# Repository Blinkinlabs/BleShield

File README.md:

# Blinkinlabs Bluetooth Low Energy Shield

An Arduino shield using the S-Power BG312L BLE module:
http://s-power.com.hk/BG312L.html

This shield is designed for the serial version of the module.

The BLE Shield has plenty of different peripherals that you can use to prototype your own Bluetooth Low Energy designs: three buttons, one RGB led, and an output to control one digital RGB LED strip.

The BLE Shield has been tested on the Arduino Duemilanove, Uno, and Leonardo. It has been confirmed to work with the iPad Mini running the free LightBlue application, and should work fine with iPhone 4S, iPhone5, and iPad Retina running iOS 5 and 6. The iPad 2 does not support Bluetooth 4.0 (BLE). Android support for BLE is unfortunately incomplete but in active development. Support for MacOS, Windows, and Linux is currently untested but seems to be in active development.

We're currently working on demo applications for iOS and computers, but in the mean time, you can communicate with your BLE Shield using the free LightBlue application by Punch Through, available on the app store. There are several other BLE iOS apps available that should work as well.

The BG312L module is based on the [TI CC2541][ti] Bluetooth 4.0 chip. More information, as well as sample iOS code, is available on [TI's Wiki][ti-wiki].

Let us know what cool things you do with the BLE Shield!

# Arduino Library and Demo Sketch

From the `library` folder, copy the `Blinkinlabs_BLEShield` folder to your Arduino `libraries` folder. Restart the Arduino IDE, then open File->Sketchbook->libraries->Blinkinlabs_BLEShield->BLEShield. Upload to your Arduino and follow the instructions on our [website][ble] to connect to the shield using your Bluetooth 4.0 compatible device. Enjoy!

[ti]: http://www.ti.com/product/cc2541
[ti-wiki]: http://processors.wiki.ti.com/index.php/Category:BluetoothLE

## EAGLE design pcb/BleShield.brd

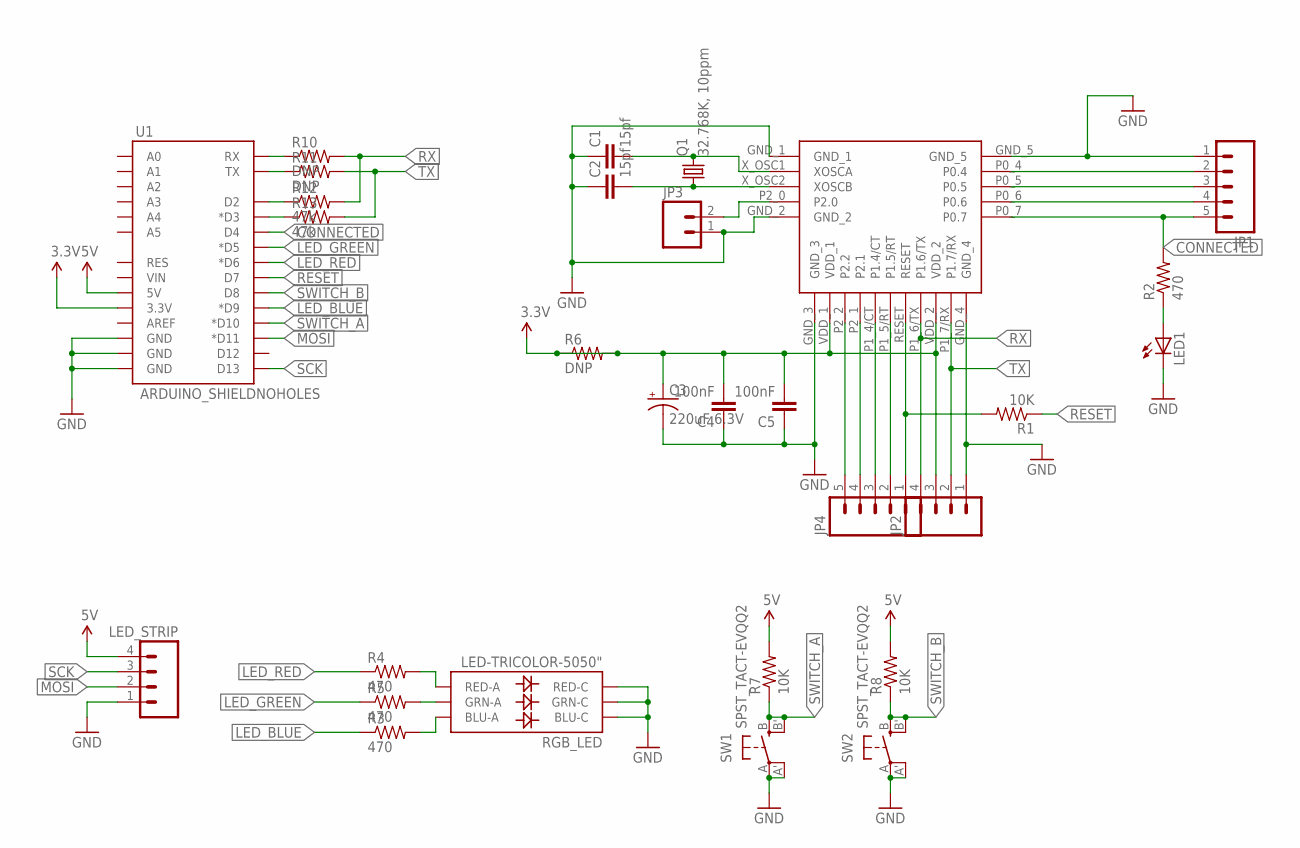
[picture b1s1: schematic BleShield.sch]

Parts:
C1, C2: 15pf; 0805
C3: 220uF 6.3V; C/6032-28R
C4, C5: 100nF; 0805
JP1, JP4: M051.27MM; 1X05-1.27MM
JP2: M041.27MM; 1X04-1.27MM
JP3: M02; 1X02-1.27MM
LED1: LEDCHIPLED_0805; CHIPLED_0805
LED_STRIP: M04PTH; 1X04
Q1: 32.768K, 10ppm; CRYSTAL_3215
R1, R7, R8: 10K; 0805
R2, R3, R4, R5: 470; 0805
R6, R10, R11: DNP; 0805
R12, R13: 47k; 0805
RGB_LED: LED-TRICOLOR-5050"; LED-TRICOLOR-5050-FIXED
SW1, SW2: SPST_TACT-EVQQ2; EVQ-Q2
U1: ARDUINO_SHIELDNOHOLES; DUEMILANOVE_SHIELD_NOHOLES
U$1: BG213L; BG312L

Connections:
3.3V: C3.+, C4.2, C5.2, JP2.3, R6.1, R6.2, U1.3.3V, U$1.VDD_1, U$1.VDD_2
5V: LED_STRIP.4, R7.2, R8.2, U1.5V
CONNECTED: JP1.5, R2.2, U1.D4, U$1.P0_7 (P0.7)
GND: C1.1, C2.1, C3.-, C4.1, C5.1, JP1.1, JP2.1, JP3.1, LED1.C, LED_STRIP.1, RGB_LED.1 (BLU-C), RGB_LED.2 (RED-C), RGB_LED.3 (GRN-C), SW1.A, SW1.A' (P1), SW2.A, SW2.A' (P1), U1.GND@0 (GND), U1.GND@1 (GND), U1.GND@2 (GND), U$1.GND_1, U$1.GND_2, U$1.GND_3, U$1.GND_4, U$1.GND_5
LED_BLUE: R3.1, U1.D9 (*D9)
LED_GREEN: R5.1, U1.D5 (*D5)
LED_RED: R4.1, U1.D6 (*D6)
MOSI: LED_STRIP.2, U1.D11 (*D11)
unnamed: JP4.1, R1.2, U$1.RESET
unnamed: R3.2, RGB_LED.6 (BLU-A)
unnamed: C1.2, Q1.P$2 (2), U$1.X_OSC1 (XOSCA)
unnamed: C2.2, Q1.P$1 (1), U$1.X_OSC2 (XOSCB)
unnamed: R5.2, RGB_LED.4 (GRN-A)
unnamed: R4.2, RGB_LED.5 (RED-A)
unnamed: LED1.A, R2.1
unnamed: JP4.5, U$1.P2_2 (P2.2)
unnamed: R12.1, U1.D2
unnamed: R10.1, U1.RX
unnamed: R11.1, U1.TX
unnamed: JP4.4, U$1.P2_1 (P2.1)
unnamed: JP4.3, U$1.P1_4/CT (P1.4/CT)
unnamed: JP4.2, U$1.P1_5/RT (P1.5/RT)
unnamed: JP1.2, U$1.P0_4 (P0.4)
unnamed: JP1.3, U$1.P0_5 (P0.5)
unnamed: JP1.4, U$1.P0_6 (P0.6)
unnamed: JP3.2, U$1.P2_0 (P2.0)
unnamed: R13.1, U1.D3 (*D3)
RESET: R1.1, U1.D7
RX: JP2.4, R10.2, R12.2, U$1.P1_6/TX (P1.6/TX)
SCK: LED_STRIP.3, U1.D13
SWITCH_A: R7.1, SW1.B (S), SW1.B' (S1), U1.D10 (*D10)
SWITCH_B: R8.1, SW2.B (S), SW2.B' (S1), U1.D8
TX: JP2.2, R11.2, R13.2, U$1.P1_7/RX (P1.7/RX)

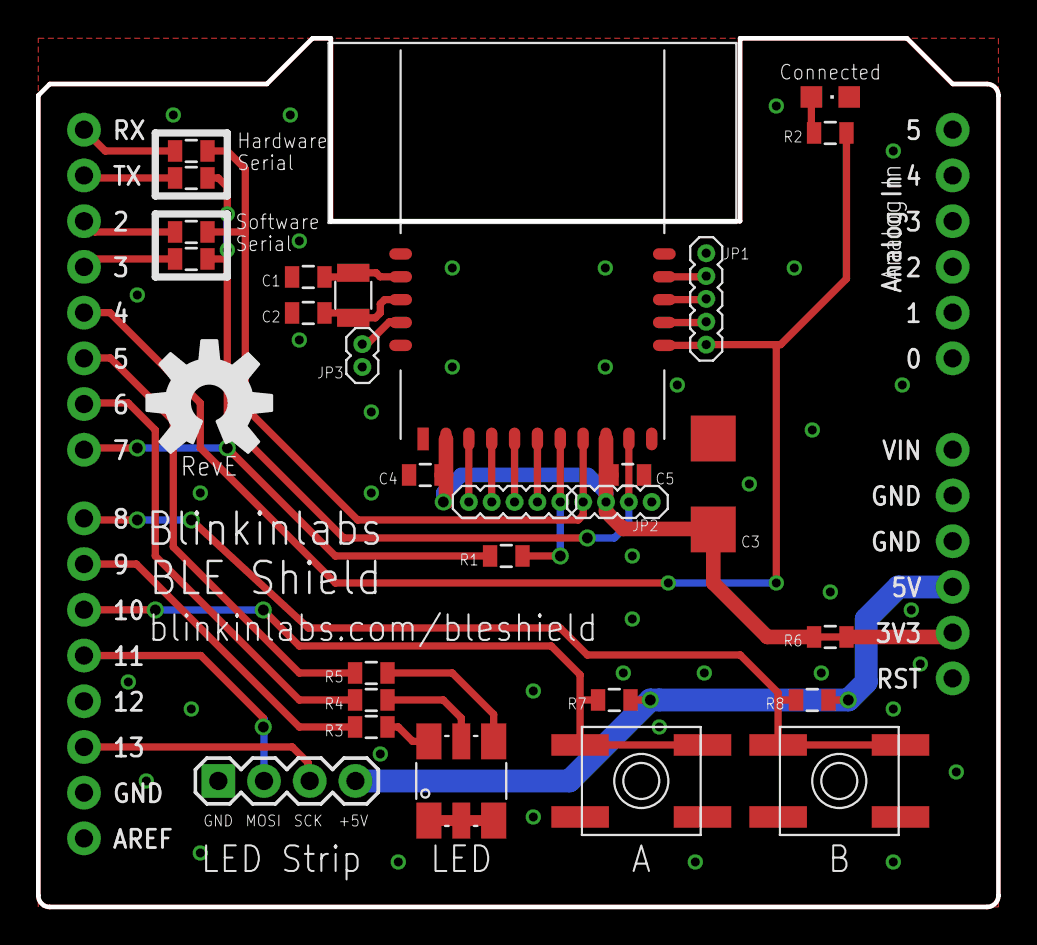
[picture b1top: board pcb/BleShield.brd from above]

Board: 2 copper layers, 53.3 x 48.3 mm, 30 parts (0 on the bottom side), 33 nets.

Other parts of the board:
U$7: OSHW-LOGO-L

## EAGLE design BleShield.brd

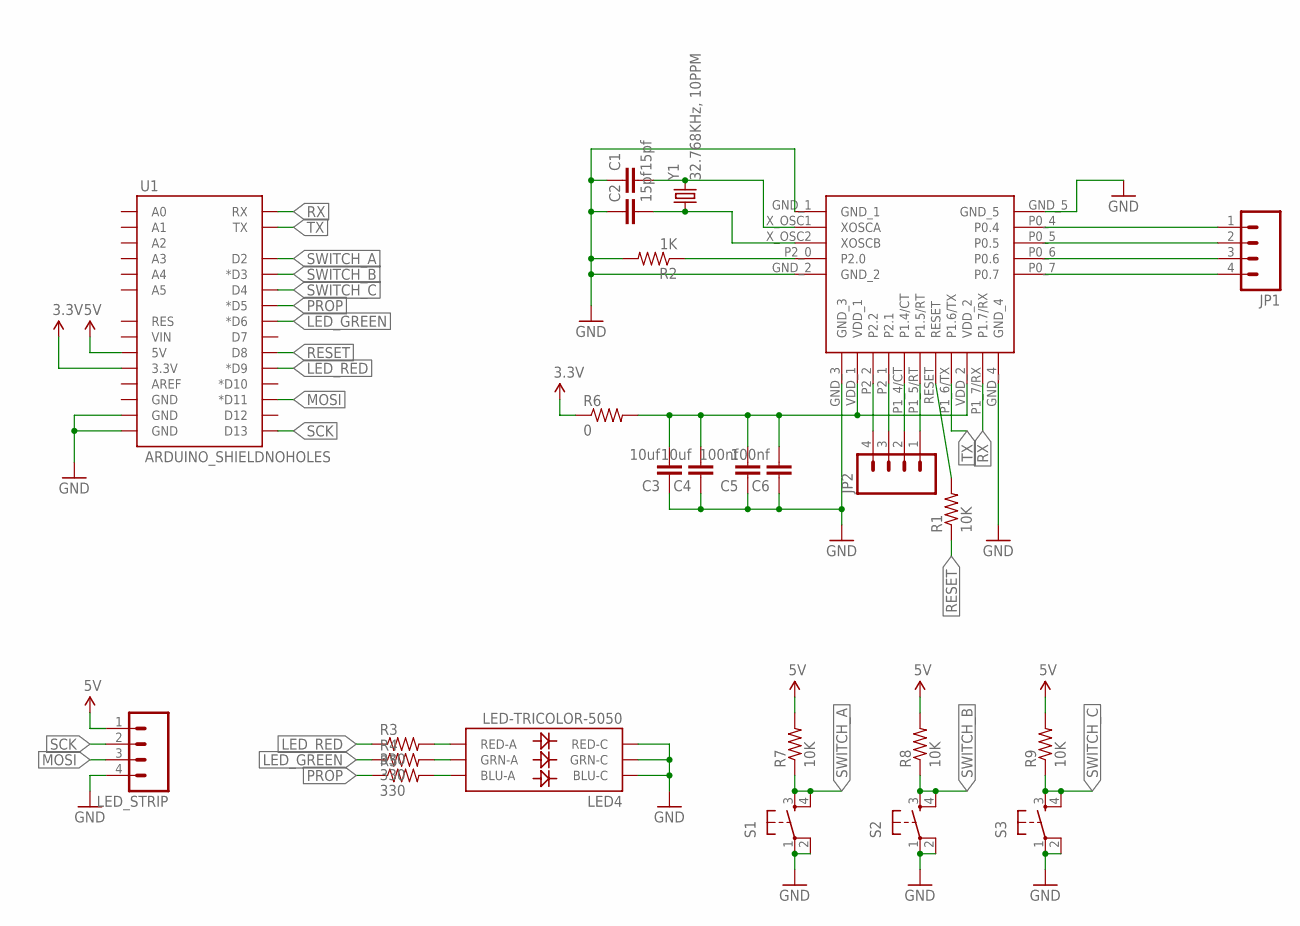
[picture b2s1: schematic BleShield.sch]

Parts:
C1, C2: 15pf; 0805
C3, C4: 10uf; 0805
C5, C6: 100nf; 0805
JP1, JP2: M04PTH; 1X04
LED4: LED-TRICOLOR-5050
LED_STRIP: M04PTH; 1X04
R1, R7, R8, R9: 10K; 0805
R2: 1K; 0805
R3, R4, R5: 330; 0805
R6: 0; 0805
S1, S2, S3: TAC_SWITCHSMD; TACTILE_SWITCH_SMD
U1: ARDUINO_SHIELDNOHOLES; DUEMILANOVE_SHIELD_NOHOLES
U$1: BG213L; BG312L
Y1: 32.768KHz, 10PPM; CRYSTAL-32KHZ-SMD

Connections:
3.3V: R6.1, U1.3.3V
5V: LED_STRIP.1, R7.2, R8.2, R9.2, U1.5V
GND: C1.1, C2.1, C3.1, C4.1, C5.1, C6.1, LED4.4 (BLU-C), LED4.5 (RED-C), LED4.6 (GRN-C), LED_STRIP.4, R2.2, S1.1, S1.2, S2.1, S2.2, S3.1, S3.2, U1.GND@0 (GND), U1.GND@1 (GND), U$1.GND_1, U$1.GND_2, U$1.GND_3, U$1.GND_4, U$1.GND_5
LED_GREEN: R4.1, U1.D6 (*D6)
LED_RED: R3.1, U1.D9 (*D9)
MOSI: LED_STRIP.3, U1.D11 (*D11)
unnamed: R1.2, U$1.RESET
unnamed: R2.1, U$1.P2_0 (P2.0)
unnamed: C1.2, U$1.X_OSC1 (XOSCA), Y1.X2 (2)
unnamed: C2.2, U$1.X_OSC2 (XOSCB), Y1.X1 (1)
unnamed: LED4.2 (RED-A), R3.2
unnamed: LED4.1 (GRN-A), R4.2
unnamed: LED4.3 (BLU-A), R5.2
unnamed: C3.2, C4.2, C5.2, C6.2, R6.2, U$1.VDD_1, U$1.VDD_2
unnamed: JP1.1, U$1.P0_4 (P0.4)
unnamed: JP1.2, U$1.P0_5 (P0.5)
unnamed: JP1.3, U$1.P0_6 (P0.6)
unnamed: JP1.4, U$1.P0_7 (P0.7)
unnamed: JP2.1, U$1.P1_5/RT (P1.5/RT)
unnamed: JP2.2, U$1.P1_4/CT (P1.4/CT)
unnamed: JP2.3, U$1.P2_1 (P2.1)
unnamed: JP2.4, U$1.P2_2 (P2.2)
PROP: R5.1, U1.D5 (*D5)
RESET: R1.1, U1.D8
RX: U1.RX, U$1.P1_7/RX (P1.7/RX)
SCK: LED_STRIP.2, U1.D13
SWITCH_A: R7.1, S1.3, S1.4, U1.D2
SWITCH_B: R8.1, S2.3, S2.4, U1.D3 (*D3)
SWITCH_C: R9.1, S3.3, S3.4, U1.D4
TX: U1.TX, U$1.P1_6/TX (P1.6/TX)

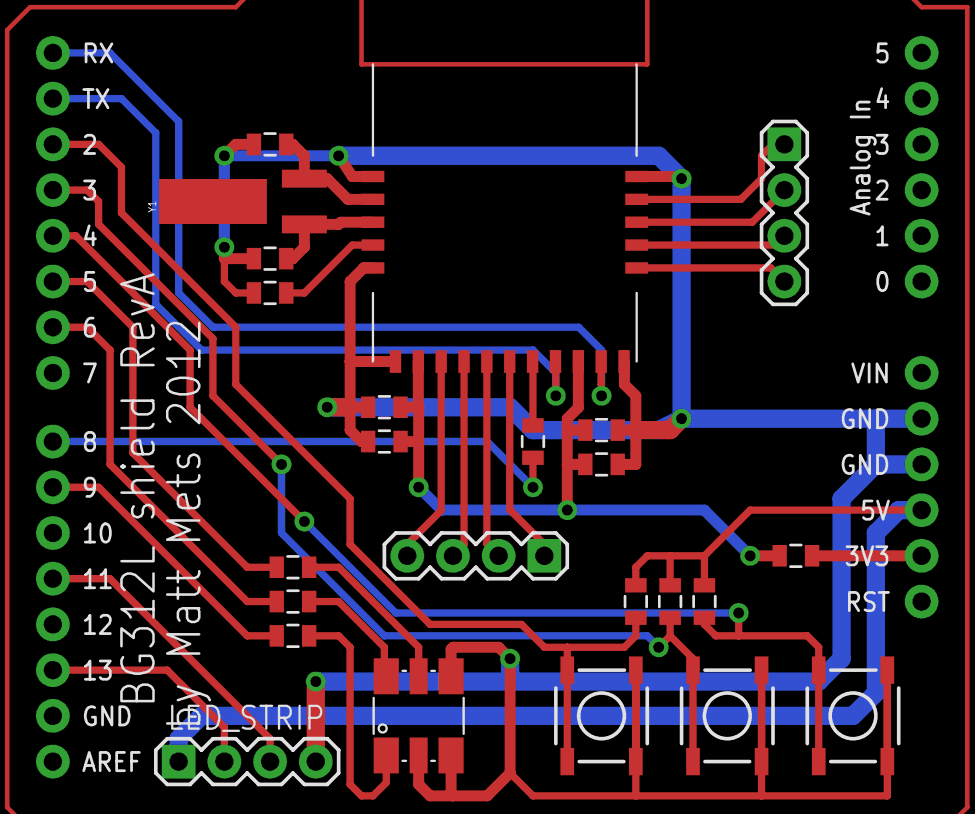
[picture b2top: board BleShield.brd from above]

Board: 2 copper layers, 25 parts (0 on the bottom side), 30 nets.

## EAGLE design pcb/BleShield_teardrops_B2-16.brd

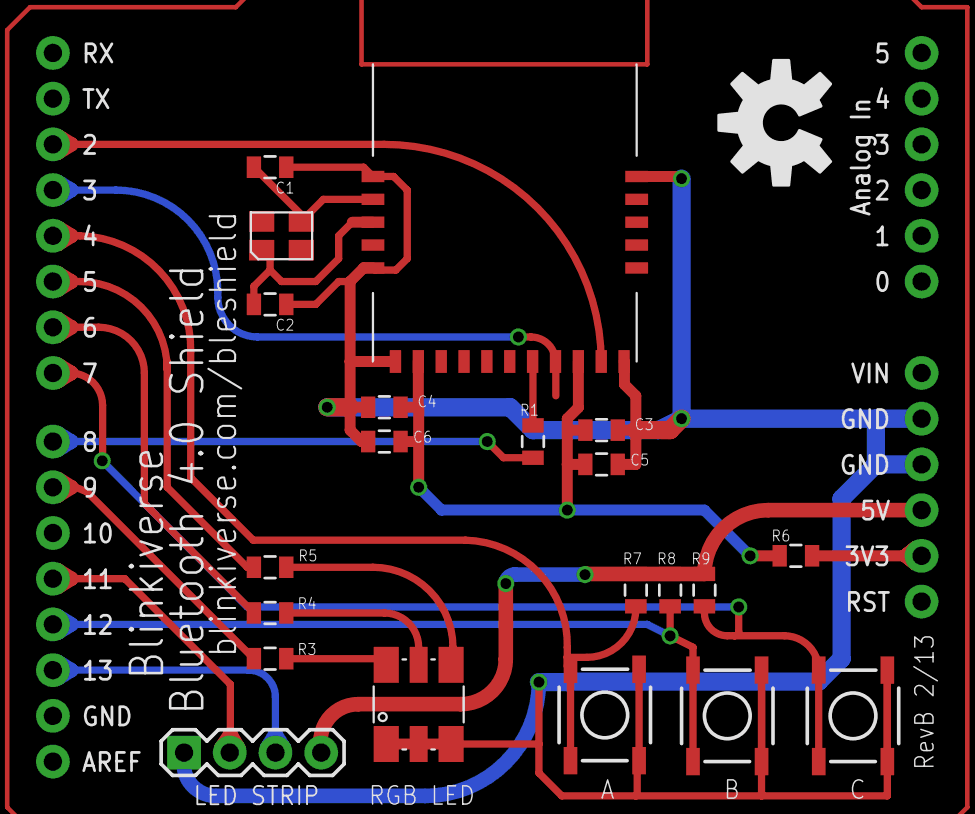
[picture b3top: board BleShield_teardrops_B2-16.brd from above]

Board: 2 copper layers, 23 parts (0 on the bottom side), 21 nets.

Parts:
A: TACTILE_SWITCH_SMD
B: TACTILE_SWITCH_SMD
C: TACTILE_SWITCH_SMD
C1, C2: 15pf; 0805
C3, C4: 10uf; 0805
C5, C6: 100nf; 0805
LED STRIP: 1X04
R1, R7, R8, R9: 10K; 0805
R3, R4, R5: 330; 0805
R6: 0; 0805
RGB LED: LED-TRICOLOR-5050"; LED-TRICOLOR-5050-FIXED
U1: ARDUINO_SHIELDNOHOLES; DUEMILANOVE_SHIELD_NOHOLES
U$1: BG213L; BG312L
U$7: OSHW-LOGO-L
Y1: 32.768KHz, 10 PPM; XS3225

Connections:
3.3V: R6.1, U1.3.3V
5V: LED STRIP.4, R7.2, R8.2, R9.2, U1.5V
GND: A.1, A.2, B.1, B.2, C.1, C.2, C1.1, C2.1, C3.1, C4.1, C5.1, C6.1, LED STRIP.1, RGB LED.1, RGB LED.2, RGB LED.3, U1.GND@0, U1.GND@1, U$1.GND_1, U$1.GND_2, U$1.GND_3, U$1.GND_4, U$1.GND_5
LED_BLUE: R3.1, U1.D9
LED_GREEN: R5.1, U1.D5
LED_RED: R4.1, U1.D6
MOSI: LED STRIP.2, U1.D11
unnamed: R1.2, U$1.RESET
unnamed: R3.2, RGB LED.6
unnamed: C1.2, U$1.X_OSC1, Y1.P$3
unnamed: C2.2, U$1.X_OSC2, Y1.P$1
unnamed: R5.2, RGB LED.4
unnamed: R4.2, RGB LED.5
unnamed: C3.2, C4.2, C5.2, C6.2, R6.2, U$1.VDD_1, U$1.VDD_2
RESET: R1.1, U1.D8
RX: U1.D2, U$1.P1_7/RX
SCK: LED STRIP.3, U1.D13
SWITCH_A: A.3, A.4, R7.1, U1.D4
SWITCH_B: B.3, B.4, R8.1, U1.D12
SWITCH_C: C.3, C.4, R9.1, U1.D7
TX: U1.D3, U$1.P1_6/TX

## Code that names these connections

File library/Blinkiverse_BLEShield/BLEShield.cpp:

#include "BLEShield.h"
#include "Arduino.h"

#define SOFTWARE_RX_PIN 2
#define SOFTWARE_TX_PIN 3

#define LED_RED   6
#define LED_BLUE  9
#define LED_GREEN 5

#define RESET_PIN     7
#define CONNECTED_PIN 4

#define SWITCH_A 10
#define SWITCH_B 8

#define TACK 0
#define RACK 1
#define GARBAGE 2

uint8_t expectedTransmitACK[5] = {0x02, 0x80, 0x01, 0x00, 0x81};
uint8_t expectedRecieveACK[3] = {0x02, 0x20, 0xDD};

SoftwareSerial _bleSerial(SOFTWARE_RX_PIN, SOFTWARE_TX_PIN);

BLEShield::BLEShield(void) {
  pinMode(SOFTWARE_RX_PIN, INPUT);
  pinMode(SOFTWARE_TX_PIN, OUTPUT);
  
  // Set the switch pins to inputs
  pinMode(CONNECTED_PIN, INPUT);  
  pinMode(SWITCH_A, INPUT);
  pinMode(SWITCH_B, INPUT);

   // Enable the reset output
  digitalWrite(RESET_PIN, HIGH);
  pinMode(RESET_PIN, OUTPUT);

  // Reset the BLE module  
  digitalWrite(RESET_PIN, LOW);
  _delay_ms(100);
  digitalWrite(RESET_PIN, HIGH);

  _bleSerial.begin(9600);
  _bleSerial.listen();

}

void BLEShield::setLED(uint8_t R, uint8_t G, uint8_t B) {
  analogWrite(LED_RED,    R);
  analogWrite(LED_GREEN,  G);
  analogWrite(LED_BLUE,   B);
}

// // Debugging
void BLEShield::dumpBuffer(uint8_t buffer[]) {
  for (int x=0; x < 64; x++) {
    Serial.print(buffer[x], HEX);
    Serial.print(" ");
  }
  Serial.println();
}

// Flash the RED Led
void BLEShield::errorFlash() {
 for (int x=0; x < 4; x++) {
    setLED(255,0,0);
    _delay_ms(75);    
    setLED(0,0,0);
    _delay_ms(75);
  }
}

int BLEShield::parse(uint8_t buffer[]) {
  for (uint8_t x=0; x < 64; x++) {

    int tack = 0;
    int rack = 0;

    // Look for a TACK
    for (uint8_t y=0; y < 5; y++) {
      if (buffer[x + y] != expectedTransmitACK[y]) {
        tack++;
      }
    }

    // Look for a RACK
    for (uint8_t y=0; y < 3; y++) {
      if (buffer[x + y] != expectedRecieveACK[y]) {
        rack++;
      }
    }

    // End of data found
    if (buffer[x] == 0xFF) {
      continue;
    }

    if (rack == 0) return RACK;
    else if (tack == 0) return TACK;
    else return GARBAGE;
  }
  return GARBAGE;
}

void BLEShield::readBLE(uint8_t buffer[]) {
  // Zero the buffer
  for(int x = 0; x < 64; x++) {
    buffer[x] = 0xFF;
  }

  // Make sure we got all the data
  _delay_ms(50);

  // Read all the data
  for(int x = 0; x < 64 && _bleSerial.available(); x++) {
    buffer[x] = _bleSerial.read();
  }  
}

void BLEShield::print(const char *str){
  setLED(0,255,0);  // All good!
  
  boolean error = false;

  int exOR_result = 0xFD;
  int dataLength = 0;

  // Calculate the length of the message
  for(dataLength=0; str[dataLength]!=0; dataLength++);

  // We can handle a maximum of 20 bytes, so bail if it's too long
  if(dataLength > 20) {
    setLED(0,0,0);
    return;
  }

  // Flush the software serial buffer, in case there was stuff in it
  _bleSerial.flush();
  
  _bleSerial.write(0xFF); // Wake up
  _bleSerial.write(0xFF); // Wake up
  _bleSerial.write(0xFF); // Wake up 
  _bleSerial.write(0x02); // Start of Packet
  _bleSerial.write(0x20); // Device
  _bleSerial.write(0xDD); // Command (send)
  _bleSerial.write(dataLength); // Length
  exOR_result = exOR_result ^ dataLength;
  for(int counter=0; counter< dataLength; counter++){
    _bleSerial.write(str[counter]); // Payload
    exOR_result = exOR_result ^ str[counter];
  }
  _bleSerial.write(exOR_result); // XOR Checksum
  
  // Wait for a reply
  _delay_ms(100);
  
  uint8_t buffer[64];
  readBLE(buffer);

  // Handle a data send failure
  if(parse(buffer) != TACK) {
    Serial.println("Error sending data to the BLE module.");
    dumpBuffer(buffer);
    errorFlash();
    return;
  }

  setLED(0,0,0);
}

// Recieve a message from the BLE shield
int BLEShield::readChars(char* inbuffer) {
  uint8_t buffer[64];
  boolean error = false;
  
  setLED(0,0,255);

  // Zero the buffer
  for(int x = 0; x < 64; x++) {
    buffer[x] = 0x00;
    inbuffer[x] = 0x00;
  }

  // Make sure we got all the data
  _delay_ms(50);

  // Read all the data   
  readBLE(buffer);  
  int resp = parse(buffer);
  
  setLED(0, 0, 0);
  
  // Handle recieve errors. TODO: XOR Checksum
  if (resp != RACK) {
    Serial.println("Error receiving data from the BLE module.");
    dumpBuffer(buffer);
    errorFlash();
    return 0;
  }
  
  // Copy the payload bytes to the provided char array
  int length = buffer[3];
  char payload[length];
  for (int x = 0; x < length; x++) {
    inbuffer[x] = (char)buffer[4 + x];
  }
  
  return length;
}

int BLEShield::available() {
  return _bleSerial.available();
}

bool BLEShield::connected() { 
  return digitalRead(CONNECTED_PIN);
}

bool BLEShield::readSwitchA() {    
  return !digitalRead(SWITCH_A);
}

bool BLEShield::readSwitchB() {    
  return !digitalRead(SWITCH_B);
}

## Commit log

2012-12-16 Working version
2012-12-16 Move PCB design to its own directory.
2012-12-16 Preliminary design finished.
2012-12-17 Add option to use software serial port, make the board smaller, etc.
2012-12-17 label most of the things
2012-12-20 Updat bom
2012-12-31 Add todo for Rev B
2012-12-31 RevA version, as shipped.
2013-01-15 Remove R2 resistor
2013-02-08 Add firmware, more TODOs
2013-02-14 fixed LED pinout, changed crystal to 3225 package
2013-02-14 messed with the silkscreens
2013-02-15 fixed silkscreens, minor re-routing, added teardrops
2013-02-16 fixed LED strip header, minor re-routing
2013-02-16 adding .gitignore
2013-02-16 re-did teardrops
2013-02-16 added code to drive the LED strip
2013-02-16 library initial commit
2013-03-27 Update documentation, layout
2013-03-27 Update TODO with specs for RevC
2013-03-27 Add keepaway, cutout to BLE part, knock out some to-do items.
2013-03-27 Swap out programming headers to 1.27mm, to match module pitch (only a master will use these anyway?)
2013-03-30 Knocked out everything except crystal pad and RX/TX doublecheck.
2013-04-01 Fix RX/TX line assignment
2013-04-01 RevC release candidate
2013-04-02 On Samson's recommendation, add ground planes on top&bottom layers under module.
2013-04-11 Add 47K resistor to work around the voltage difference problem
2013-04-11 Update firmware. Still need an ack check
2013-04-12 Moar changes
2013-04-12 Firmware extended to support bi-directional communication
2013-04-14 Moved the demo code into the library, updated READMEs
2013-04-14 accidentally a word
2013-04-23 parse() fix: Don't return undefined value.
    When buffer is filled with 0xFF, parse() should return GARBAGE rather than an undefined value.
2013-04-23 Prevent buffer overflow
    If the serial is configured incorrectly, it's possible for more bytes to be available than the buffer holds. This prevents the overflow.
2013-10-03 Name change
2013-10-07 Add the library back in!
2013-10-07 Update library name

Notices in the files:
parts and their libraries:
SparkFun: Licensing: CC v3.0 Share-Alike You are welcome to use this library for commercial purposes.
